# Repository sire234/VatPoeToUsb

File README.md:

# PoE → USB-Host-HID-Bridge (poe_usb_hid_bridge) – Rev 4g

Ein Gerät, das über **ein Ethernet-Kabel mit PoE (IEEE 802.3af)** gespeist wird und an einem **USB-A-Host-Port** ein HID-Gerät (Tastatur, Barcode-Scanner, Maus) betreibt. Die HID-Daten stellt die Firmware über Ethernet bereit.

| | |
|---|---|
| Stand | **Rev 4g** (2026-10-26: MagJack-LEDs wieder beschaltet, R5/R6; Rev 4f: D11 normale grüne LED statt WS2812B, C64 entfällt; Schaltplan mit Leitungen gezeichnet, Pin-1-Punkte im Bestückungsdruck) auf Basis **Rev 4e** inkl. Review-Korrekturen K1/H1, 2026-10-23 · **2. Review (2026-10-23):** Funktion HID → USB → MCU → Ethernet und PoE → 5 V bestätigt, keine KRITISCH/HOCH-Befunde in der Schaltung, K1/H1 verifiziert; Bohrdaten-Nullpunkt, U4-Wärme-Vias und USB-GND-Stitching behoben |
| Board | 20 × 80 mm, 6 Lagen, 1,6 mm (JLC06161H-3313), beidseitig bestückt, für ein **Kunststoffrohr** Innen-Ø 25 mm (**max. 40 °C Umgebung** empfohlen) |
| PoE | Silvertel **Ag9905-LPB** (802.3af Class 0, isoliert 5 V / 1,4 A), Brücken MB6S, TVS SMAJ58A · speisende PSE muss **IEEE 802.3af/at ≥ 48 V** sein (kein passives 24-V-PoE) |
| MCU + Ethernet | WIZnet **W55RP20** (RP2040 + W5500 + 2 MB Flash); 12 MHz Abracon ABM8-272-T3 + 2 × 15 pF (RPi-Referenz); RX über Koppel-C C65/C66 6,8 nF (WIZnet „connected CT") |
| USB | USB-A-Host, TPS2553-Lastschalter (532–659 mA), USBLC6-ESD |
| Status | MagJack-LEDs an J1 (grün = Link ← U5 LINKLED, gelb = Activity ← U5 ACTLED, aktiv low, R5/R6 330 Ω an +3V3) und eine **grüne 0603-LED** D11 (MEIHUA MHT193CGCT, 569 nm) an GPIO28 über R38 330 Ω, High = an (≈ 3,5 mA) |
| Debug | nur **SWD** über Randpads J3 (1 SWCLK, 2 GND, 3 SWDIO, 4 +3V3) für eine 2,54-mm-Stiftleiste |
| Prüfstatus | ERC 0 Fehler / 0 Warnungen · DRC (2026-10-23 13:47) 0 Errors / 0 Unconnected / 0 Parity, 23 Warnungen (nur Silkscreen/Bibliothek) |
| Bauteile | 85 Referenzen / 46 Netze → 75 Positionen bei JLC + U1 beigestellt (9 DNP inkl. J3/U1, TP9 nur Pad) · ≈ 25 USD/Board bei 10 Stk |

## Ordnerstruktur (gültige Dateien)

```text
PoeToUSB/
├── README.md                      dieser Überblick
├── SPEC.md                        Anforderungen (Stand Rev 4e)
├── pipeline_state.json            Pipeline-Status
├── architecture/
│   ├── block_diagram.md           Blöcke B1–B7, Isolationsgrenze
│   ├── net_plan.md                alle Netze, Pin-für-Pin je Block, Netzklassen
│   ├── ic_selection.md            Bauteilwahl und Begründungen
│   ├── skeleton_bom.md            funktionale Stückliste je Block, Auslegung R25
│   ├── power_budget.md            Strom-/Leistungs-/Wärmebudget
│   ├── mechanical_concept.md      Rohr, Höhenhülle, Platzierung, Stackup
│   └── design_risks.md            offene Risiken, Review-Befunde, Entscheidungen OD-1…13
├── sourcing/sourced_bom.md        Einkaufs-BOM (85 Refs, LCSC/MPN/Kosten)
├── datasheets/                    Datenblätter + *_SUMMARY.md, Index README.md
├── circuits/poe_usb_hid_bridge/   SKiDL-Quellcode (Quelle der Wahrheit)
│   ├── __main__.py                Zusammenbau, ERC, Netzlisten-Export
│   ├── ethernet_magjack.py        B1
│   ├── poe_pd_module.py           B2
│   ├── ldo_3v3.py                 B4
│   ├── mcu_w55rp20.py             B5
│   ├── usb_host_port.py           B6
│   └── status_led.py              B7
├── libs/poe_usb_hid_bridge.kicad_sym          Projekt-Symbole
├── footprints/poe_usb_hid_bridge.pretty/      Projekt-Footprints
├── kicad/poe_usb_hid_bridge_rev4g/            KiCad-10-Projekt (Schaltplan mit Leitungen + Board); ältere Revisionen nur noch in der Git-Historie
├── mechanical/
│   ├── gehaeuse_eckig_rev1/                   eckiges Gehäuse (Wanne + Deckel), make_script.py = Quelle beider Varianten
│   └── gehaeuse_eckig_rev1_swd/               dito mit seitlicher Aussparung für die SWD-Stiftleiste J3 (--swd)
├── firmware/                                  Pico-SDK-Firmware (TinyUSB-Host, W5500, mDNS, Ventile), blinky/, hwtest/
├── tools/valve-scan/                          .NET-Tool: Bridges per mDNS finden, Ventile lesen, Dauertest
└── outputs/
    ├── poe_usb_hid_bridge_rev4g.net           Netzliste
    ├── poe_usb_hid_bridge_rev4g_bom.xml       BOM (SKiDL-XML)
    ├── poe_usb_hid_bridge_rev4g_erc.txt       ERC-Protokoll (SKiDL)
    ├── poe_usb_hid_bridge_rev4g_schematic.pdf Schaltplan-PDF (mit Leitungen)
    ├── layout_rev4g/                          3D-Renders (oben, unten, iso, Detail Pin-1-Punkte, R5/R6)
    └── fab_rev4g_release/                     Fertigungsdaten (Gerber, Drill, BOM, CPL) – gültig
```

Ältere Revisionen (Netzlisten, Layouts, Fab-Daten Rev 3–4d, Snapshots) liegen noch im Projekt, gelten aber nicht mehr.

## Projekt öffnen

1. **KiCad 10** starten → `kicad/poe_usb_hid_bridge_rev4g/poe_usb_hid_bridge_rev4g.kicad_pro` öffnen. Die Projekt-Bibliotheken sind über die lokalen `sym-lib-table`/`fp-lib-table` eingebunden.
2. Der Schaltplan ist hierarchisch (ein Sheet je Block: `ethernet_magjack`, `poe_pd_module`, `ldo_3v3`, `mcu_w55rp20`, `usb_host_port`, `status_led`).
3. Netzliste neu erzeugen (optional): in `circuits/` mit installiertem SKiDL `python -m poe_usb_hid_bridge` ausführen → schreibt `outputs/poe_usb_hid_bridge_rev4g.net` und `_bom.xml` (KiCad-10-Bibliothekspfade sind in `__main__.py` gesetzt).

## Fertigungsdaten

Ort: **`outputs/fab_rev4g_release/`** (Gerber, Bohrdaten, JLC-BOM und -CPL, ZIP `poe_usb_hid_bridge_rev4g_gerber_drill.zip`; Stand 2026-10-26; DRC 0 Errors / 0 Unconnected / 0 Parity, 18 Warnungen Silkscreen/J1). **Nicht verwenden:** `fab_rev4f_final/` und `fab_rev4g_final/` – dort liegen die Gerber auf absoluten Koordinaten, die Bohrdaten auf dem Board-Ursprung (100 mm Versatz, Review 2026-10-26). U1 ist im JLC-Export DNP (Beistellteil), J3 (SWD-Randpads), TP9 und alle DNP-Optionen erscheinen nicht in der CPL.

**Behobener Exportfehler (2026-10-23):** Die Bohrdaten hatten einen anderen Nullpunkt als die Gerbers (Versatz 100 mm, Board-Ursprung bei 100/100). Bohrdaten wurden mit `--drill-origin plot` neu exportiert, das ZIP neu gepackt. Bei jedem Neu-Export so vorgehen (KiCad 10, im Ordner `kicad/poe_usb_hid_bridge_rev4e/`):

```text
kicad-cli pcb export gerbers --use-drill-file-origin --layers "F.Cu,In1.Cu,In2.Cu,In3.Cu,In4.Cu,B.Cu,F.Paste,B.Paste,F.Silkscreen,B.Silkscreen,F.Mask,B.Mask,Edge.Cuts" -o ../../outputs/fab_rev4g_release/gerber/ poe_usb_hid_bridge_rev4g.kicad_pcb
kicad-cli pcb export drill --format excellon --drill-origin plot --excellon-separate-th --generate-map --map-format gerberx2 -o ../../outputs/fab_rev4g_release/gerber/ poe_usb_hid_bridge_rev4g.kicad_pcb
```

**Wichtig:** Gerber immer mit `--use-drill-file-origin` exportieren, Bohrdaten mit `--drill-origin plot` – beide liegen dann auf dem Board-Ursprung (Ecke RJ45-Seite, X0 … 80).

- Gerber und Bohrdaten müssen denselben Nullpunkt haben (`plot`); im JLC-Gerber-Viewer prüfen, dass die Bohrungen auf den Pads liegen.
- **Nicht `--board-plot-params` verwenden:** Im Board ist der Plotparameter `drillshape=1` gesetzt → Bohrmarken in den Kupferlagen. Entweder ohne Board-Plotparameter exportieren oder `drillshape` vorher auf 0 setzen.
- **Bei J1 nicht „Footprints aus Bibliothek aktualisieren"**: Der J1-Footprint ist lokal angepasst (verkleinerte Pads/ISO-Keepout, R-ISO-3); die DRC-Warnung `lib_footprint_mismatch` ist deshalb gewollt.
- DRC (13:47): 0 Errors / 0 Unconnected / 0 Parity, 23 Warnungen (Silkscreen, J1-Bibliotheksabgleich).

## Bestell-Checkliste (JLCPCB)

- [ ] **6 Lagen, 1,6 mm, Stackup JLC06161H-3313** wählen; Lagenbelegung In1 GND, In2 VBUS, In3 +5V, In4 +3V3.
- [ ] **Impedanzkontrolle** bestellen: ETH 100 Ω diff. (0,13 / 0,2 mm), USB 90 Ω diff. (0,15 / 0,18 mm) – mit dem JLC-Impedanzrechner für JLC06161H-3313 gegenprüfen.
- [ ] **Vias:** Standard 0,45/0,3 mm; in der Rule-Area `U5_FANOUT` **3 Vias 0,4/0,2 mm mit 0,1 mm Abstand** → entsprechende Fertigungsoption (Aufpreis; optional vorher durch 0,45/0,3 ersetzen, dann entfällt er).
- [ ] **Via-in-Pad gefüllt und gedeckelt (POFV)** – im Board nicht als Attribut gesetzt → bei der Bestellung wählen und diese **POFV-Liste** beilegen (Koordinaten x/y in mm, Board-Ursprung = Ecke RJ45-Seite):
  - *Via-Mitte im Pad:* U1 Pad 1 × 2 (41,6/4,2; 42,4/4,2), C52.1 (62,32/13,56), U4-EP × 3 (49,15/14,04; 49,15/14,60; 49,15/15,16).
  - *Via-Rand berührt Pad:* U5.54 (60,79/12,25), C55.1 (59,34/4,68), R22.1 (57,05/4,2), C50.2 (49,6/10,3).
- [ ] **U1 Ag9905-LPB beistellen** (DigiKey 5061-AG9905-LPB-ND) → JLC-Consignment-SMT, sonst Handreflow; **nur Oberseite**. Für Consignment **U1 in BOM und CPL aufnehmen** (im aktuellen Export DNP).
- [ ] **Paste auf DNP-Pads:** Die Pastenschablone druckt auch auf die Pads von U1, C1, C14, R8, R9, C30 → bei JLC akzeptieren bzw. Hinweis geben (U1-Consignment braucht die Paste).
- [ ] **CPL-Rotationen** sind KiCad-Winkel → im JLC-Placement-Viewer jede Lage prüfen, besonders U5, U4, U6, U7, C11, C18, D1–D3, D12, D11, Y1/Y2. Bei **Y1/Y2 nach Datenblatt-Pin-1 ausrichten, nicht nach der Fase** – eine 90°-Fehllage legt die Quarzpins auf GND.
- [ ] **Lagerbestand (live 2026-10-23):** **W55RP20 C43229502 nur 89 Stk → bei JLC reservieren!** · ABM8-272-T3 C20625731 3 388 · HR871150C C19724786 328 · USB-A C18077687 488. C65/C66 (C93654) und C25/C26 15 pF (C1548) in der JLC-BOM kontrollieren.
- [ ] **D11 grüne LED (C2962098):** Polarität (Kathode = Pad 1, in der Draufsicht unten) im JLC-Placement-Viewer prüfen; kein Backen mehr nötig (WS2812B entfallen).
- [ ] **Footprint-1:1-Prüfungen** mit Ausdruck: U1 (Ag9905-LPB, Pin-1-Lage!), J1 (HR871150C), J2 (BX-TYPE-A-MWT4P); zusätzlich U5-Land-Pattern.
- [ ] J1 ist THT → JLC-THT-Lötservice; **20 Extended-Typen** (≈ 60 USD/Bestellung).
- [ ] **Optional (Review-Empfehlung, Hipot):** R7 statt 0603 als 1206-HV-Widerstand – im aktuellen Board nicht umgesetzt (design_risks R-ISO-8).
- [ ] **Speisung klären:** Router/Switch/Injektor muss **IEEE 802.3af/at mit ≥ 48 V** liefern; passives 24-V-PoE funktioniert nicht.
- [ ] **Gehäuse:** Kunststoffrohr Innen-Ø 25 mm, Endkappen mit Lüftungsschlitzen; Einsatz bei **max. 40 °C Umgebung** einplanen.
- [ ] Vor dem Bestellen Stock/Preise in `sourcing/sourced_bom.md` neu prüfen.

## Inbetriebnahme

1. **Erstes Einschalten:** normgerechter **802.3af/at-PoE-Injektor bzw. -Switch (≥ 48 V)**, idealerweise mit Strombegrenzung – kein passives 24-V-PoE; +5V an TP9 und +3V3 an J3 Pin 4 messen (Erwartung: 4,75–5,25 V bzw. 3,30 V; Leerlauf ≈ 180 mA an +5V_RAW mit Link).
2. **Programmierung nur über SWD:** 1×4-Stiftleiste (2,54 mm) liegend auf die Randpads J3 löten, Pins ragen über die Board-Kante: Pin 1 SWCLK, 2 GND, 3 SWDIO, 4 +3V3. Pins 1–3 entsprechen der SWD-Reihenfolge des Raspberry Pi Pico bzw. des 3-Pin-Kabels der Raspberry Pi Debug Probe (OpenOCD `rp2040.cfg`); +3V3 nur als Referenz, das Board über PoE versorgen. Es gibt keinen BOOTSEL-Taster, kein UART und keinen Reset-Pin – der USB-A-Port ist Host und taugt nicht für den USB-Bootloader.
3. **Firmware:** Pico-SDK + **TinyUSB-Host** (`tuh_hid_*`) + **WIZnet ioLibrary** (W5500 über das interne PIO-SPI des W55RP20; GPIO20–25 intern).
   - GPIO26 = `USB_EN` (aktiv-high, Default AUS), GPIO28 = `LED_DIN` (normaler GPIO-Ausgang, High = grüne LED an; PWM möglich), GPIO29/ADC3 = `VBUS_SENSE` (Faktor 0,405).
   - `PICO_BOARD`, Flash-Grösse 2 MB und boot2 wie beim **WIZnet W55RP20-EVB** einstellen.
   - W5500-Anbindung (verifiziert, WIZnet-PICO-C): CS 20, SCK 21, MISO 22, MOSI 23, INT 24, RST 25 über PIO-SPI (`USE_PIO`). Die Status-LED braucht seit Rev 4f keinen PIO mehr.
   - Überlast über `VBUS_SENSE` erkennen: **Schwelle ≈ 4,0–4,2 V** (nicht 4,5 V – im Normalbetrieb sind Worst Case ≈ 4,6 V möglich), Messwert mitteln und **> 50 ms entprellen**, dann `USB_EN` abschalten (Retry mit Backoff).
   - Nach `USB_EN = 0` entlädt sich VBUS nur über den Teiler (τ ≈ 27 s): vor einem Neustart des Ports warten bzw. per `VBUS_SENSE` prüfen, dass VBUS abgefallen ist.
   - MagJack-LEDs (Rev 4g) werden direkt vom W5500 angesteuert (Link grün, Activity gelb) – keine Firmware nötig. Link-Status zusätzlich über **PHYCFGR** lesbar.
   - Status-LED: ≈ 3,5 mA bei Dauer-An, kein Einfluss auf das +3V3-Budget.
   - Quarz Y1 entspricht der Raspberry-Pi-Referenz (ABM8-272-T3, 2 × 15 pF, 1 kΩ); `PICO_XOSC_STARTUP_DELAY_MULTIPLIER` kann auf dem SDK-Default bleiben (64 als Reserve schadet nicht).
4. Danach PoE vom Ziel-Router/-Switch (802.3af/at, ≥ 48 V): Detection, Link 10/100, USB-Gerät anstecken.
5. **Thermik prüfen:** im geschlossenen Kunststoffrohr bei Volllast (USB 0,5 A) und USB-Kurzschluss die Temperaturen an U1, U5, U4 und J1 messen; Betrieb nur bis **40 °C Umgebung** (W55RP20 Tc ≤ 85 °C, J1 ≤ 70 °C).
6. **R9 (VBUS-Abgleich) nur bei Bedarf:** +5V_RAW höchstens 5,25 V – R9 = 0 Ω (5,65 V) ist unzulässig.

## Offene Prüfpunkte am Muster

| Punkt | Was prüfen | Option |
|---|---|---|
| **Thermik** | Temperatur an U1, U5, U4, J1 im geschlossenen Rohr bei Volllast und USB-Kurzschluss (erwartet ≈ 68–80 °C bei 40 °C Umgebung) | Kunststoffrohr: Umgebung ≤ 40 °C, Lüftungsschlitze in den Endkappen; Isolation zum Rohr unkritisch. U4 hat jetzt 3 Thermal-Vias im EP + 2 GND-Vias |
| **VBUS / R9** | VBUS am Port unter 0,5 A (Worst Case ≈ 4,6 V) | R9 ADJ → GND bestücken, Ziel +5V_RAW ≈ 5,10 V, **max. 5,25 V** (R9 = 0 Ω → 5,65 V unzulässig) |
| **PoE-Detection / C1** | Detection mit 2–3 verschiedenen PSEs | C1 bleibt DNP; nur bei Bedarf bestücken |
| **Hipot 1500 VAC** | Isolation primär ↔ sekundär inkl. J1-Pfad (R-ISO-3, R-ISO-7, ETH_RXN 1,8 mm zu J1.7 R-ISO-9); Modul ist für 1500-V-DC-Impuls spezifiziert | C24 DNP als Option; R7 0603 ist im Hipot überlastet → 1206-HV empfohlen (R-ISO-8) |
| **Mindestlast / R8** | Geräusch im Leerlauf (< 200 mA) | R8 100 Ω (1206) bestücken |
| **RUN-Pull-up** | Störfestigkeit ohne externen Reset-Pull-up/C | 10 k (+ 100 nF) von RUN (U5.29) an +3V3 nachrüsten |
| **Ethernet** | Link 10/100, Paketverlust bei 100 m (RX jetzt mit C65/C66); W5500-Stabilität (C61 nicht direkt an TOCAP, Abblock Pin 42/43 > 5 mm) | siehe design_risks R-ETH-1, R-LAY-7, R-PI-12 |
| **Mechanik** | D3 (SMA, Bottom) hat nur ≈ 0,25 mm Reserve zur Rohrwand; J2 laut Datenblatt 15,2 mm breit (Laschen) / 7,0 mm hoch | Einbau ins Rohr vorsichtig prüfen |
| Weitere | Quarz-Anlauf kurz kontrollieren, USB-Signalqualität, LED-Helligkeit an 3,3 V, D11-Polarität | siehe `architecture/design_risks.md` §4 (offene Review-Empfehlungen) |

## Revisionsverlauf (Kurz)

Rev 1–3 diskreter Flyback (TPS23753A + POE70P) · Rev 3 30-mm-Board verworfen · Rev 4 Ag9905LP-Modul · Rev 4b WS2812B + Tag-Connect · Rev 4c Brücken-Variante verworfen · Rev 4d Minimal-Debug (nur SWD), LED an +3V3 · **Rev 4e Ag9905-LPB (SMT)** · Rev 4e Review: K1 RX-Koppel-C C65/C66, H1 Quarz nach RPi-Referenz, Kunststoffrohr ≤ 40 °C · **Rev 4f** D11 normale grüne LED (C64 entfällt), ganzer Schaltplan mit Leitungen, Pin-1-Punkte, 3D-Modelle U1/U5/J1/J2 · **Rev 4g** MagJack-LEDs wieder beschaltet (R5/R6, Leitungen auf In3).

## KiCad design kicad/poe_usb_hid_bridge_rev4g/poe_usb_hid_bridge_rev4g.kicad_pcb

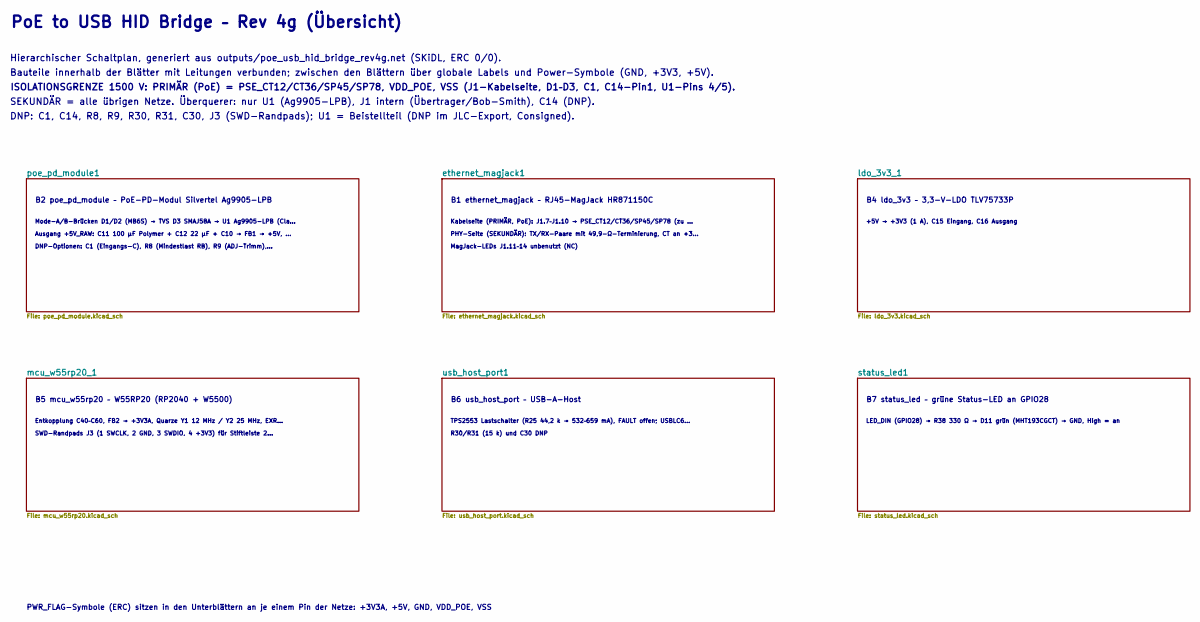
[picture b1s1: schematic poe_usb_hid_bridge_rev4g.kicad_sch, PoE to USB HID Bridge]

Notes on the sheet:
PoE to USB HID Bridge – Rev 4g (Übersicht)
Hierarchischer Schaltplan, generiert aus outputs/poe_usb_hid_bridge_rev4g.net (SKiDL, ERC 0/0).
Bauteile innerhalb der Blätter mit Leitungen verbunden; zwischen den Blättern über globale Labels und Power-Symbole (GND, +3V3, +5V).
ISOLATIONSGRENZE 1500 V: PRIMÄR (PoE) = PSE_CT12/CT36/SP45/SP78, VDD_POE, VSS (J1-Kabelseite, D1–D3, C1, C14-Pin1, U1-Pins 4/5).
SEKUNDÄR = alle übrigen Netze. Überquerer: nur U1 (Ag9905-LPB), J1 intern (Übertrager/Bob-Smith), C14 (DNP).
DNP: C1, C14, R8, R9, R30, R31, C30, J3 (SWD-Randpads); U1 = Beistellteil (DNP im JLC-Export, Consigned).
B2 poe_pd_module – PoE-PD-Modul Silvertel Ag9905-LPB
Mode-A/B-Brücken D1/D2 (MB6S) → TVS D3 SMAJ58A → U1 Ag9905-LPB (Cla…
Ausgang +5V_RAW: C11 100 µF Polymer + C12 22 µF + C10 → FB1 → +5V, …
DNP-Optionen: C1 (Eingangs-C), R8 (Mindestlast RB), R9 (ADJ-Trimm),…
B1 ethernet_magjack – RJ45-MagJack HR871150C
Kabelseite (PRIMÄR, PoE): J1.7–J1.10 → PSE_CT12/CT36/SP45/SP78 (zu …
PHY-Seite (SEKUNDÄR): TX/RX-Paare mit 49,9-Ω-Terminierung, CT an +3…
MagJack-LEDs J1.11–14 unbenutzt (NC)
B4 ldo_3v3 – 3,3-V-LDO TLV75733P
+5V → +3V3 (1 A), C15 Eingang, C16 Ausgang
B5 mcu_w55rp20 – W55RP20 (RP2040 + W5500)
Entkopplung C40–C60, FB2 → +3V3A, Quarze Y1 12 MHz / Y2 25 MHz, EXR…
SWD-Randpads J3 (1 SWCLK, 2 GND, 3 SWDIO, 4 +3V3) für Stiftleiste 2…
B6 usb_host_port – USB-A-Host
TPS2553 Lastschalter (R25 44,2 k → 532–659 mA), FAULT offen; USBLC6…
R30/R31 (15 k) und C30 DNP
B7 status_led – grüne Status-LED an GPIO28
LED_DIN (GPIO28) → R38 330 Ω → D11 grün (MHT193CGCT) → GND, High = an
PWR_FLAG-Symbole (ERC) sitzen in den Unterblättern an je einem Pin der Netze: +3V3A, +5V, GND, VDD_POE, VSS

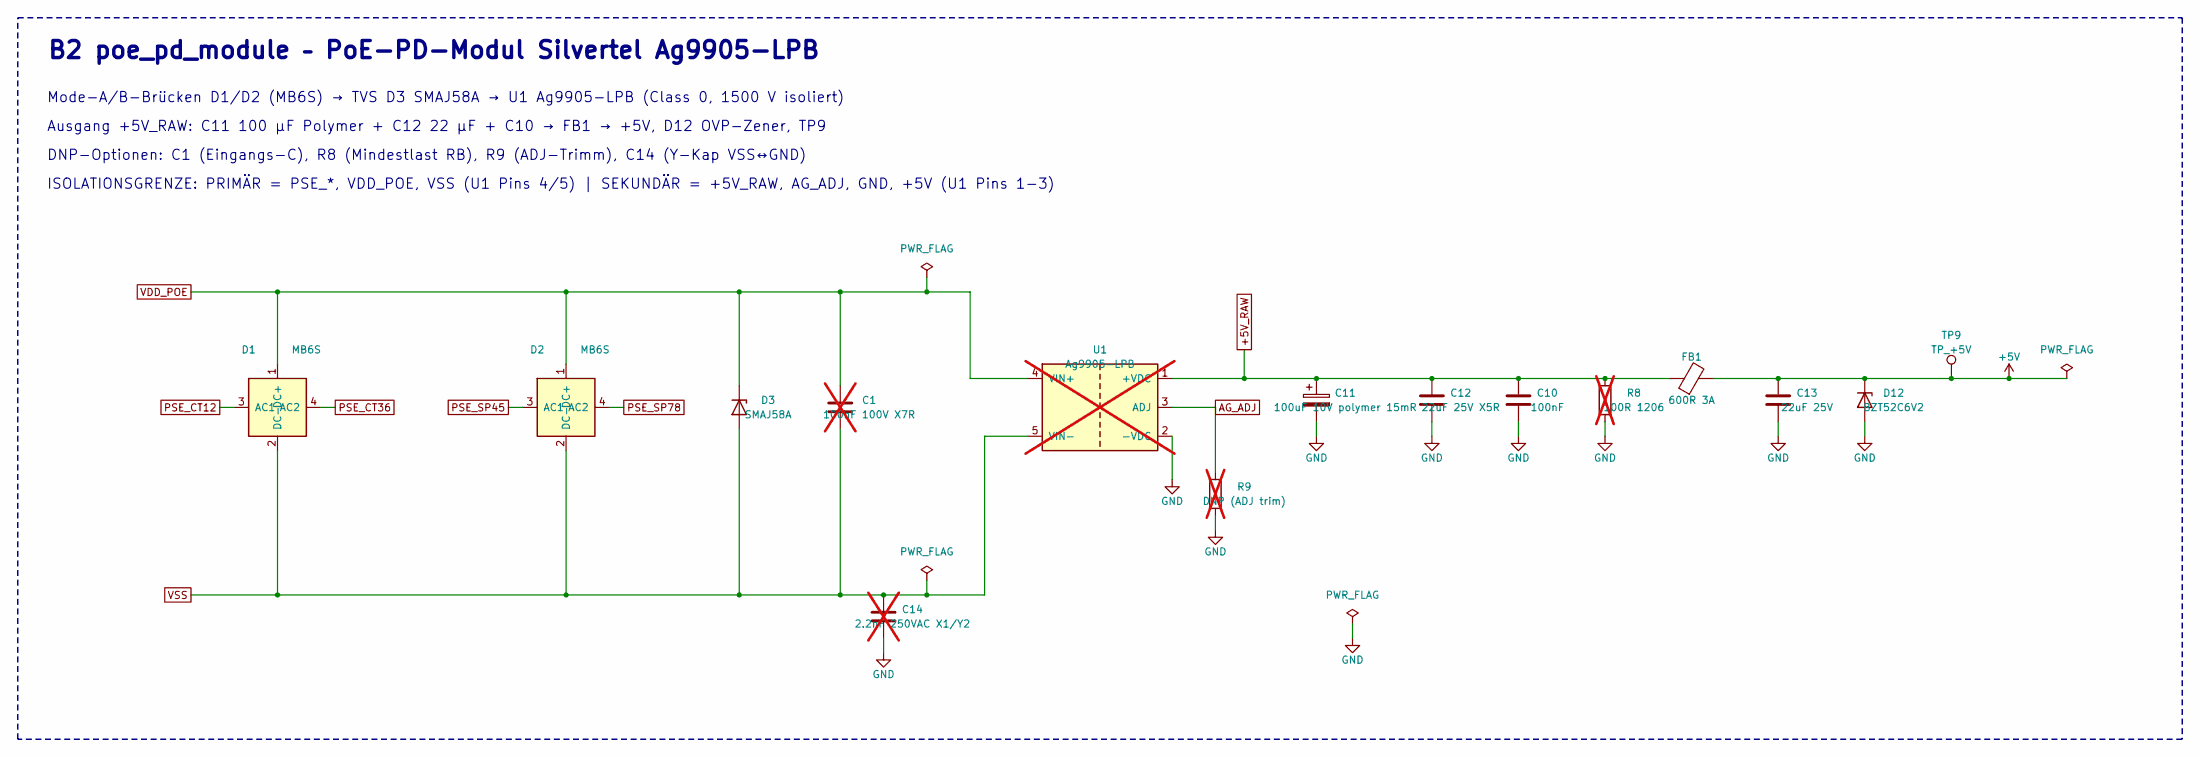
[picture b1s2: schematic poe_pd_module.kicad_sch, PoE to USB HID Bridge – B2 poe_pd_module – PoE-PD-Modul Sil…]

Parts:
C1: 100nF 100V X7R; C_0805_2012Metric; MPN CL21B104KCFNNNE; LCSC C28233; not fitted
C10: 100nF; C_0402_1005Metric; MPN CL05B104KO5NNNC; LCSC C1525
C11: 100uF 10V polymer 15mR; CP_EIA-7343-31_Kemet-D; MPN SA11AM101A19R15XXX; LCSC C135491
C12: 22uF 25V X5R; C_0805_2012Metric; MPN CL21A226MAQNNNE; LCSC C45783
C13: 22uF 25V; C_0805_2012Metric; MPN CL21A226MAQNNNE; LCSC C45783
C14: 2.2nF 250VAC X1/Y2; C_1812_4532Metric; MPN FK12X222K502EGQ; LCSC C53026446; not fitted
D1, D2: MB6S; TO-269AA; MPN MDD MB6S-50MIL; LCSC C2487
D3: SMAJ58A; D_SMA; MPN MDD SMAJ58A; LCSC C123816
D12: BZT52C6V2; D_SOD-123; MPN BZT52C6V2; LCSC C271260
FB1: 600R 3A; L_1206_3216Metric; MPN HCB3216KF-601T30; LCSC C357023
R8: 100R 1206; R_1206_3216Metric; MPN 1206W4F1000T5E; LCSC C17901; not fitted
R9: DNP (ADJ trim); R_0603_1608Metric; not fitted
TP9: TP_+5V; TestPoint_Pad_D1.0mm
U1: Ag9905-LPB; Silvertel_Ag9900LPB_SMD; MPN Ag9905-LPB; not fitted

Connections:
+5V: C13.1, D12.1 (K), FB1.2, TP9.1; also elsewhere on the board
+5V_RAW: C10.1, C11.1, C12.1, FB1.1, R8.1, U1.1 (+VDC)
AG_ADJ: R9.1, U1.3 (ADJ)
GND: C10.2, C11.2, C12.2, C13.2, C14.2, D12.2 (A), R8.2, R9.2, U1.2 (-VDC); also elsewhere on the board
PSE_CT12: D1.3 (AC1); also elsewhere on the board
PSE_CT36: D1.4 (AC2); also elsewhere on the board
PSE_SP45: D2.3 (AC1); also elsewhere on the board
PSE_SP78: D2.4 (AC2); also elsewhere on the board
VDD_POE: C1.1, D1.1 (DC+), D2.1 (DC+), D3.1 (K), U1.4 (VIN+)
VSS: C1.2, C14.1, D1.2 (DC-), D2.2 (DC-), D3.2 (A), U1.5 (VIN-)

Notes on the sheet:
B2 poe_pd_module – PoE-PD-Modul Silvertel Ag9905-LPB
Mode-A/B-Brücken D1/D2 (MB6S) → TVS D3 SMAJ58A → U1 Ag9905-LPB (Class 0, 1500 V isoliert)
Ausgang +5V_RAW: C11 100 µF Polymer + C12 22 µF + C10 → FB1 → +5V, D12 OVP-Zener, TP9
DNP-Optionen: C1 (Eingangs-C), R8 (Mindestlast RB), R9 (ADJ-Trimm), C14 (Y-Kap VSS↔GND)
ISOLATIONSGRENZE: PRIMÄR = PSE_*, VDD_POE, VSS (U1 Pins 4/5) | SEKUNDÄR = +5V_RAW, AG_ADJ, GND, +5V (U1 Pins 1-3)

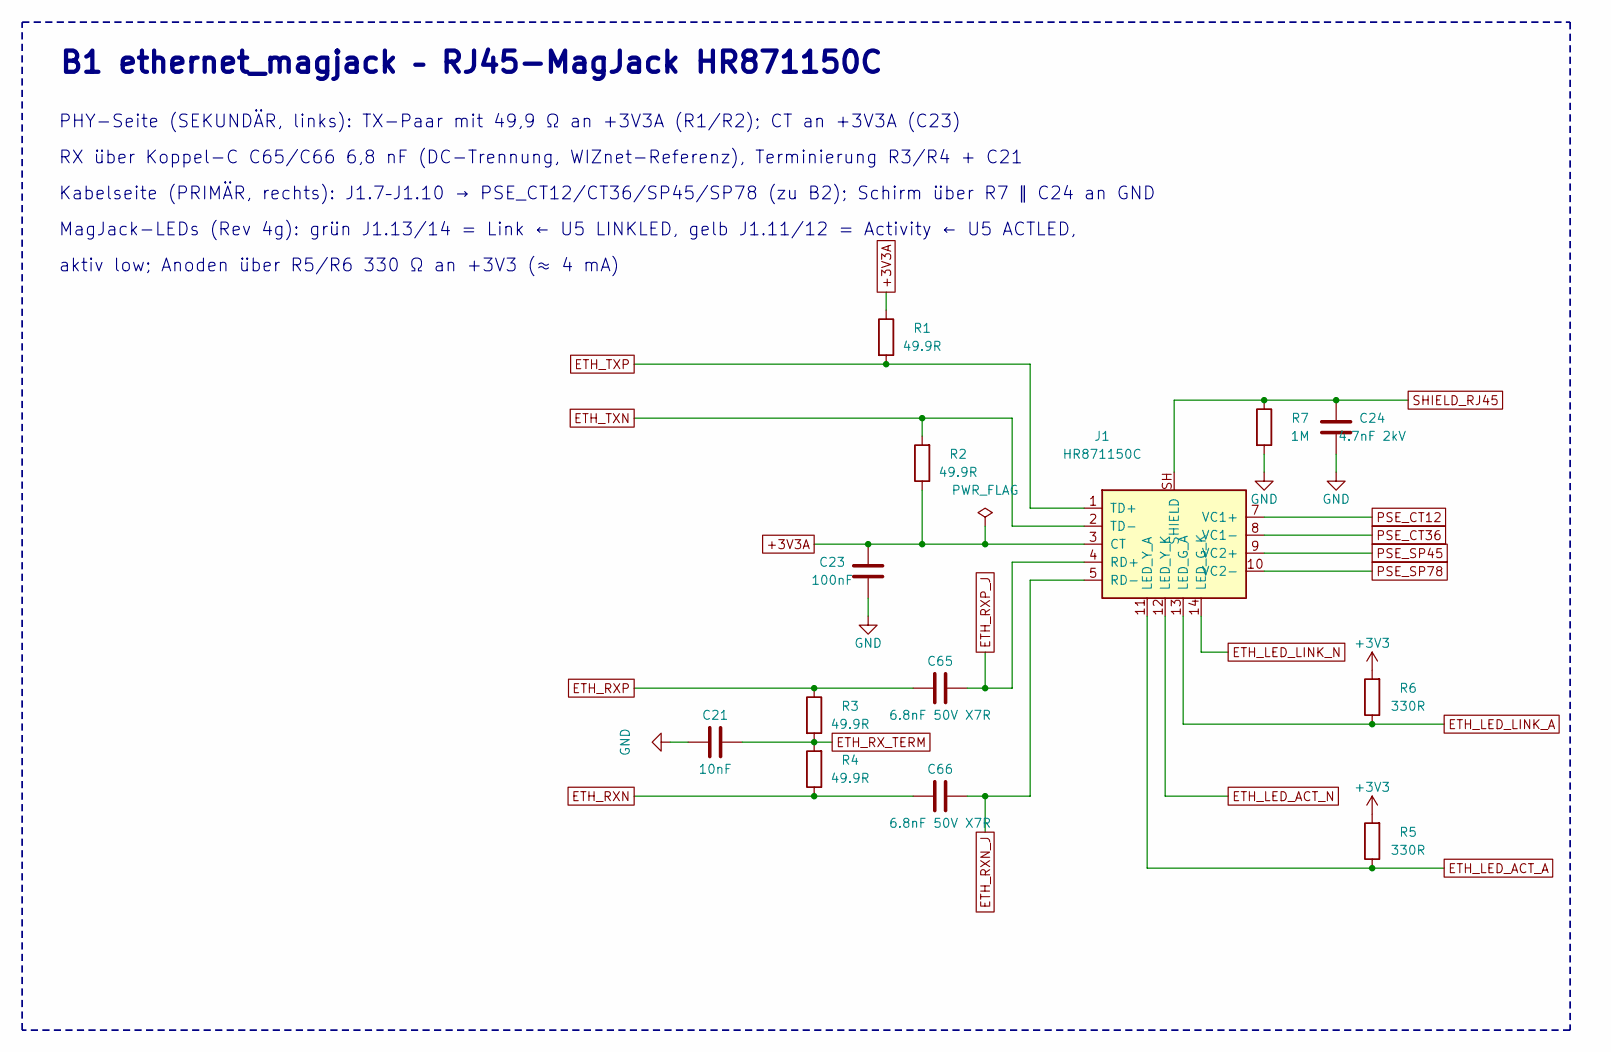
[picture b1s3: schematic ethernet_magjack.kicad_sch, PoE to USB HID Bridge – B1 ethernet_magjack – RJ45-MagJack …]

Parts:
C21: 10nF; C_0402_1005Metric; MPN CL05B103KB5NNNC; LCSC C15195
C23: 100nF; C_0402_1005Metric; MPN CL05B104KO5NNNC; LCSC C1525
C24: 4.7nF 2kV; C_1812_4532Metric; MPN C1812X472K202T; LCSC C106172
C65, C66: 6.8nF 50V X7R; C_0402_1005Metric; MPN YAGEO CC0402KRX7R9BB682; LCSC C93654
J1: HR871150C; HanRun_HR871150C; MPN HanRun HR871150C; LCSC C19724786
R1, R2, R3, R4: 49.9R; R_0402_1005Metric; MPN 0402WGF499JTCE; LCSC C25120
R5, R6: 330R; R_0402_1005Metric; MPN 0402WGF3300TCE; LCSC C25104
R7: 1M; R_0603_1608Metric; MPN 0603WAF1004T5E; LCSC C22935

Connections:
+3V3: R5.2, R6.2; also elsewhere on the board
+3V3A: C23.1, J1.3 (CT), R1.1, R2.1; also elsewhere on the board
ETH_LED_ACT_A: J1.11 (LED_Y_A), R5.1
ETH_LED_ACT_N: J1.12 (LED_Y_K); also elsewhere on the board
ETH_LED_LINK_A: J1.13 (LED_G_A), R6.1
ETH_LED_LINK_N: J1.14 (LED_G_K); also elsewhere on the board
ETH_RXN: C66.2, R4.1; also elsewhere on the board
ETH_RXN_J: C66.1, J1.5 (RD-)
ETH_RXP: C65.2, R3.1; also elsewhere on the board
ETH_RXP_J: C65.1, J1.4 (RD+)
ETH_RX_TERM: C21.1, R3.2, R4.2
ETH_TXN: J1.2 (TD-), R2.2; also elsewhere on the board
ETH_TXP: J1.1 (TD+), R1.2; also elsewhere on the board
GND: C21.2, C23.2, C24.2, R7.2; also elsewhere on the board
PSE_CT12: J1.7 (VC1+); also elsewhere on the board
PSE_CT36: J1.8 (VC1-); also elsewhere on the board
PSE_SP45: J1.9 (VC2+); also elsewhere on the board
PSE_SP78: J1.10 (VC2-); also elsewhere on the board
SHIELD_RJ45: C24.1, J1.SH (SHIELD), R7.1

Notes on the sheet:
B1 ethernet_magjack – RJ45-MagJack HR871150C
PHY-Seite (SEKUNDÄR, links): TX-Paar mit 49,9 Ω an +3V3A (R1/R2); CT an +3V3A (C23)
RX über Koppel-C C65/C66 6,8 nF (DC-Trennung, WIZnet-Referenz), Terminierung R3/R4 + C21
Kabelseite (PRIMÄR, rechts): J1.7–J1.10 → PSE_CT12/CT36/SP45/SP78 (zu B2); Schirm über R7 ∥ C24 an GND
MagJack-LEDs (Rev 4g): grün J1.13/14 = Link ← U5 LINKLED, gelb J1.11/12 = Activity ← U5 ACTLED,
aktiv low; Anoden über R5/R6 330 Ω an +3V3 (≈ 4 mA)

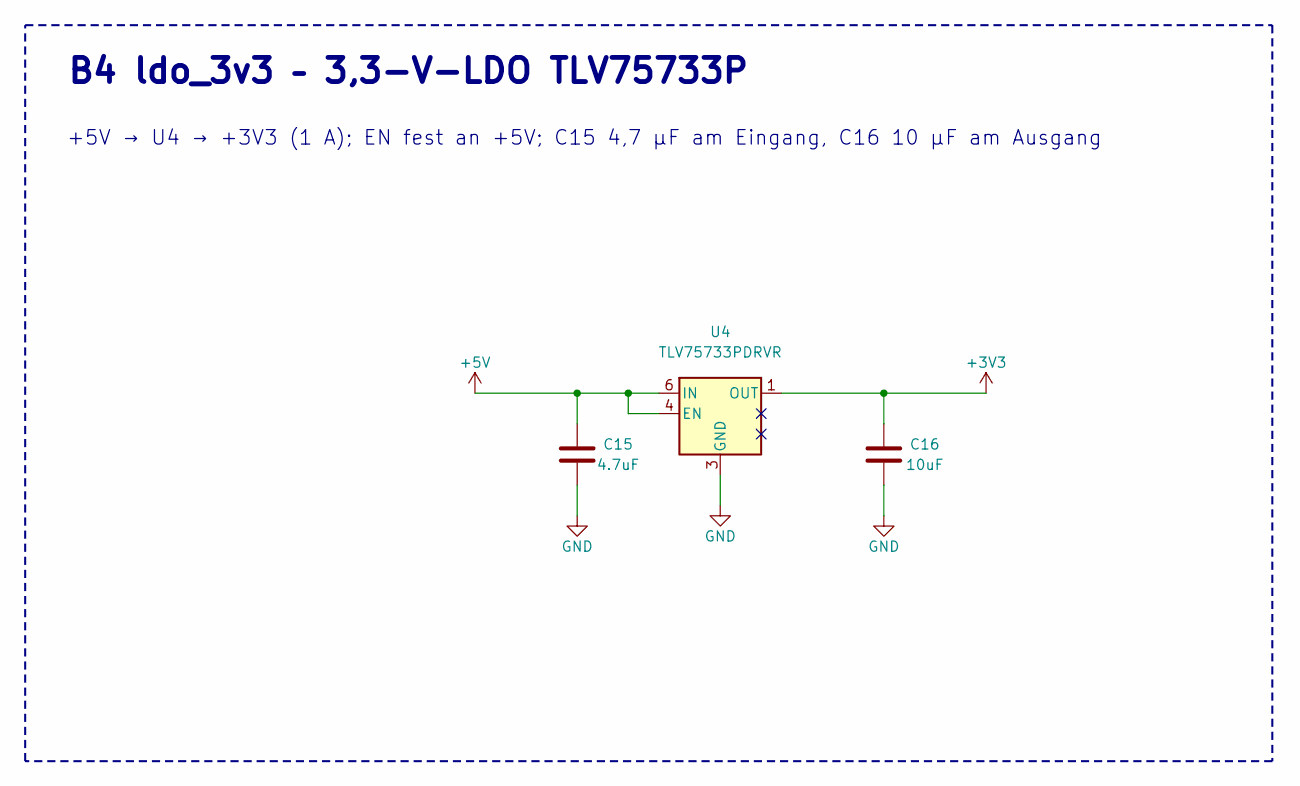
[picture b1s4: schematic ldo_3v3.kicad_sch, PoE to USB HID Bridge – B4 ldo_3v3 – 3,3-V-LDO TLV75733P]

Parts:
C15: 4.7uF; C_0603_1608Metric; MPN CL10A475KO8NNNC; LCSC C19666
C16: 10uF; C_0603_1608Metric; MPN CL10A106KP8NNNC; LCSC C19702
U4: TLV75733PDRVR; WSON-6-1EP_2x2mm_P0.65mm_EP1x1.6mm; MPN TLV75733PDRVR; LCSC C2868428

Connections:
+3V3: C16.1, U4.1 (OUT); also elsewhere on the board
+5V: C15.1, U4.4 (EN), U4.6 (IN); also elsewhere on the board
GND: C15.2, C16.2, U4.3 (GND), U4.7 (GND); also elsewhere on the board

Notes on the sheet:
B4 ldo_3v3 – 3,3-V-LDO TLV75733P
+5V → U4 → +3V3 (1 A); EN fest an +5V; C15 4,7 µF am Eingang, C16 10 µF am Ausgang

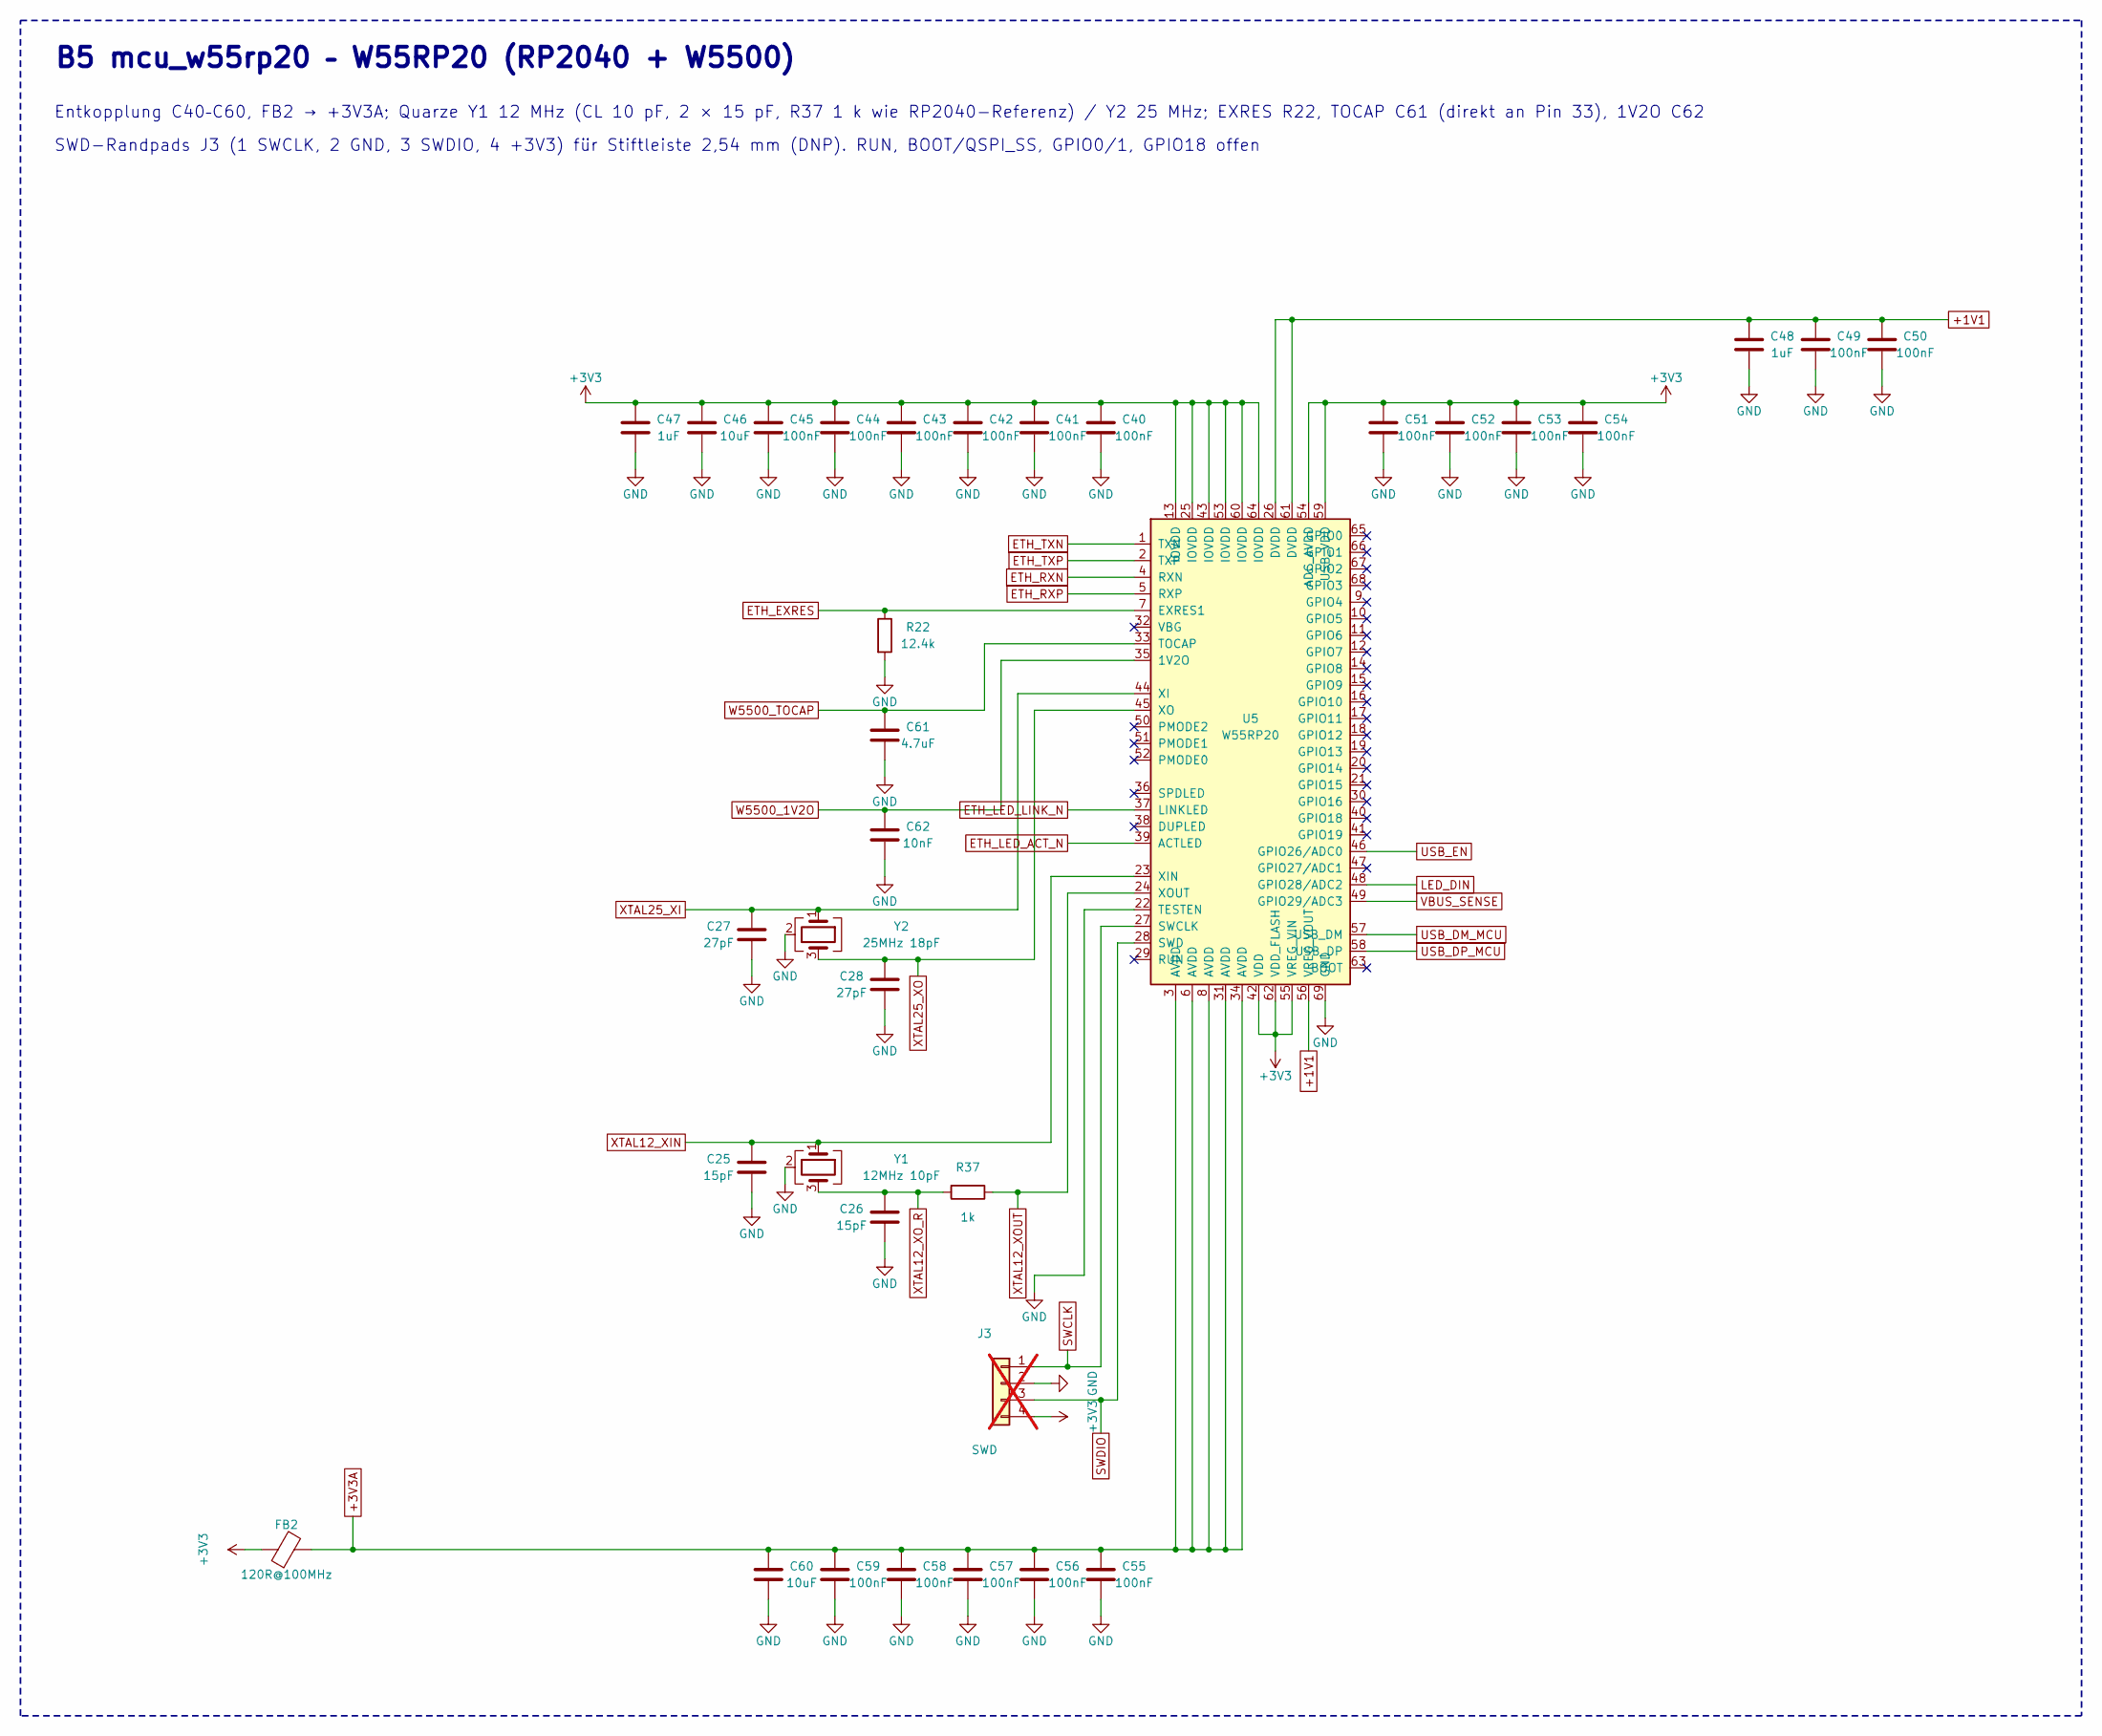
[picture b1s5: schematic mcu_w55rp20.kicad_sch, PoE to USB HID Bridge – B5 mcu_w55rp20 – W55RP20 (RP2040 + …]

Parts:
C25, C26: 15pF; C_0402_1005Metric; MPN 0402CG150J500NT; LCSC C1548
C27, C28: 27pF; C_0402_1005Metric; MPN 0402CG270J500NT; LCSC C1557
C40, C41, C42, C43, C44, C45, C49, C50, C51, C52, C53, C54, C55, C56, C57, C58, C59: 100nF; C_0402_1005Metric; MPN CL05B104KO5NNNC; LCSC C1525
C46, C60: 10uF; C_0603_1608Metric; MPN CL10A106KP8NNNC; LCSC C19702
C47, C48: 1uF; C_0402_1005Metric; MPN CL05A105KA5NQNC; LCSC C52923
C61: 4.7uF; C_0603_1608Metric; MPN CL10A475KO8NNNC; LCSC C19666
C62: 10nF; C_0402_1005Metric; MPN CL05B103KB5NNNC; LCSC C15195
FB2: 120R@100MHz; L_0603_1608Metric; MPN BLM18PG121SN1D; LCSC C14709
J3: SWD; SWD_Edge_1x04_P2.54mm_SMD; not fitted
R22: 12.4k; R_0402_1005Metric; MPN 0402WGF1242TCE; LCSC C11692
R37: 1k; R_0402_1005Metric; MPN 0402WGF1001TCE; LCSC C11702
U5: W55RP20; W55RP20_QFN-68-1EP_8x8mm_P0.4mm_EP6.2x6.2mm; MPN W55RP20; LCSC C43229502
Y1: 12MHz 10pF; Crystal_SMD_3225-4Pin_3.2x2.5mm; MPN Abracon ABM8-272-T3; LCSC C20625731
Y2: 25MHz 18pF; Crystal_SMD_3225-4Pin_3.2x2.5mm; MPN X322525MRB4SI; LCSC C70593

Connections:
+1V1: C48.1, C49.1, C50.1, U5.26 (DVDD), U5.56 (VREG_VOUT), U5.61 (DVDD)
+3V3: C40.1, C41.1, C42.1, C43.1, C44.1, C45.1, C46.1, C47.1, C51.1, C52.1, C53.1, C54.1, FB2.1, J3.4, U5.13 (IOVDD), U5.25 (IOVDD), U5.42 (VDD), U5.43 (IOVDD), U5.53 (IOVDD), U5.54 (ADC_AVDD), U5.55 (VREG_VIN), U5.59 (USB_VDD), U5.60 (IOVDD), U5.62 (VDD_FLASH), U5.64 (IOVDD); also elsewhere on the board
+3V3A: C55.1, C56.1, C57.1, C58.1, C59.1, C60.1, FB2.2, U5.3 (AVDD), U5.6 (AVDD), U5.8 (AVDD), U5.31 (AVDD), U5.34 (AVDD); also elsewhere on the board
ETH_EXRES: R22.1, U5.7 (EXRES1)
ETH_LED_ACT_N: U5.39 (ACTLED); also elsewhere on the board
ETH_LED_LINK_N: U5.37 (LINKLED); also elsewhere on the board
ETH_RXN: U5.4 (RXN); also elsewhere on the board
ETH_RXP: U5.5 (RXP); also elsewhere on the board
ETH_TXN: U5.1 (TXN); also elsewhere on the board
ETH_TXP: U5.2 (TXP); also elsewhere on the board
GND: C25.2, C26.2, C27.2, C28.2, C40.2, C41.2, C42.2, C43.2, C44.2, C45.2, C46.2, C47.2, C48.2, C49.2, C50.2, C51.2, C52.2, C53.2, C54.2, C55.2, C56.2, C57.2, C58.2, C59.2, C60.2, C61.2, C62.2, J3.2, R22.2, U5.22 (TESTEN), U5.69 (GND), Y1.2 (G), Y1.4 (G), Y2.2 (G), Y2.4 (G); also elsewhere on the board
LED_DIN: U5.48 (GPIO28/ADC2); also elsewhere on the board
SWCLK: J3.1, U5.27 (SWCLK)
SWDIO: J3.3, U5.28 (SWD)
USB_DM_MCU: U5.57 (USB_DM); also elsewhere on the board
USB_DP_MCU: U5.58 (USB_DP); also elsewhere on the board
USB_EN: U5.46 (GPIO26/ADC0); also elsewhere on the board
VBUS_SENSE: U5.49 (GPIO29/ADC3); also elsewhere on the board
W5500_1V2O: C62.1, U5.35 (1V2O)
W5500_TOCAP: C61.1, U5.33 (TOCAP)
XTAL12_XIN: C25.1, U5.23 (XIN), Y1.1
XTAL12_XOUT: R37.1, U5.24 (XOUT)
XTAL12_XO_R: C26.1, R37.2, Y1.3
XTAL25_XI: C27.1, U5.44 (XI), Y2.1
XTAL25_XO: C28.1, U5.45 (XO), Y2.3

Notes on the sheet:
B5 mcu_w55rp20 – W55RP20 (RP2040 + W5500)
Entkopplung C40–C60, FB2 → +3V3A; Quarze Y1 12 MHz (CL 10 pF, 2 × 15 pF, R37 1 k wie RP2040-Referenz) / Y2 25 MHz; EXRES R22, TOCAP C61 (direkt an Pin 33), 1V2O C62
SWD-Randpads J3 (1 SWCLK, 2 GND, 3 SWDIO, 4 +3V3) für Stiftleiste 2,54 mm (DNP). RUN, BOOT/QSPI_SS, GPIO0/1, GPIO18 offen

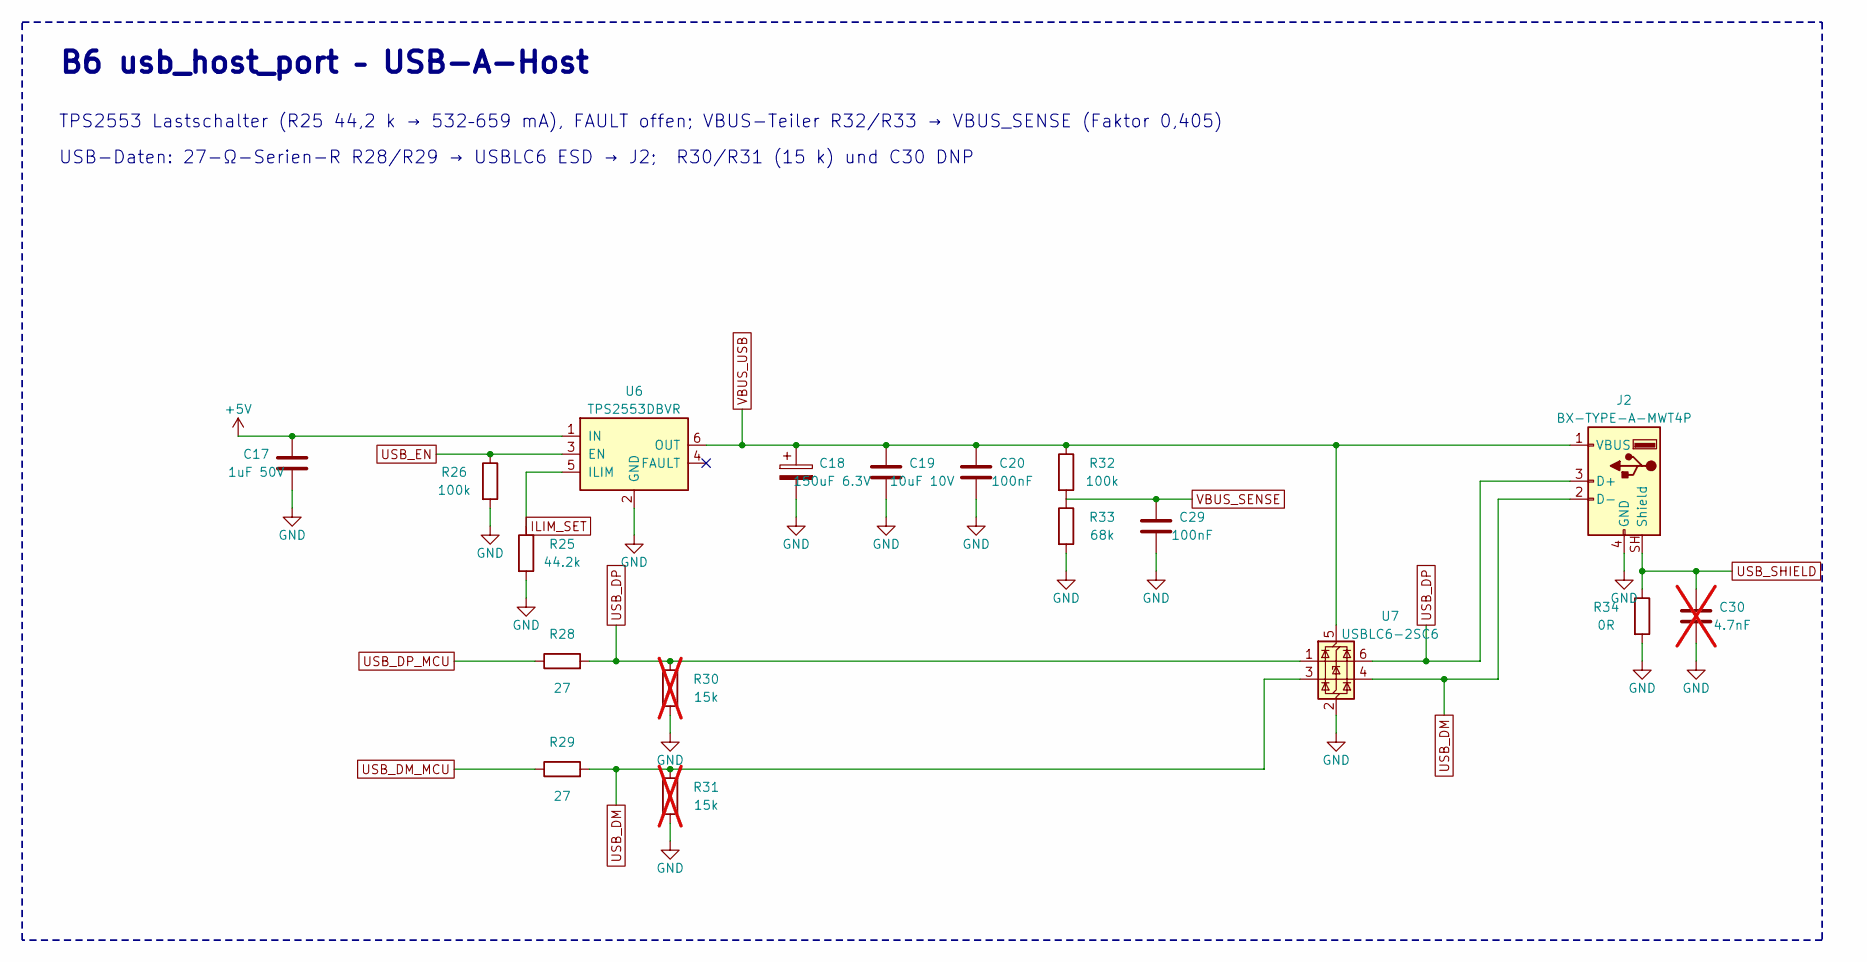
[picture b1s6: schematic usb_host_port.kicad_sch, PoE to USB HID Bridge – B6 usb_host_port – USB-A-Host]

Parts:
C17: 1uF 50V; C_0603_1608Metric; MPN CL10A105KB8NNNC; LCSC C15849
C18: 150uF 6.3V; CP_EIA-3528-21_Kemet-B; MPN T520B157M006ATE035; LCSC C212682
C19: 10uF 10V; C_0603_1608Metric; MPN CL10A106KP8NNNC; LCSC C19702
C20, C29: 100nF; C_0402_1005Metric; MPN CL05B104KO5NNNC; LCSC C1525
C30: 4.7nF; C_0603_1608Metric; MPN CL10B472KB8NNNC; LCSC C1621; not fitted
J2: BX-TYPE-A-MWT4P; MPN BX-TYPE-A-MWT4P; LCSC C18077687
R25: 44.2k; R_0402_1005Metric; MPN 0402WGF4422TCE; LCSC C25895
R26, R32: 100k; R_0402_1005Metric; MPN 0402WGF1003TCE; LCSC C25741
R28, R29: 27; R_0402_1005Metric; MPN 0402WGF270JTCE; LCSC C25100
R30, R31: 15k; R_0402_1005Metric; MPN 0402WGF1502TCE; LCSC C25756; not fitted
R33: 68k; R_0402_1005Metric; MPN 0402WGF6802TCE; LCSC C36871
R34: 0R; R_0603_1608Metric; MPN 0603WAF0000T5E; LCSC C21189
U6: TPS2553DBVR; SOT-23-6; MPN TPS2553DBVR; LCSC C55266
U7: USBLC6-2SC6; SOT-23-6; MPN USBLC6-2SC6; LCSC C7519

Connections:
+5V: C17.1, U6.1 (IN); also elsewhere on the board
GND: C17.2, C18.2, C19.2, C20.2, C29.2, C30.2, J2.4 (GND), R25.2, R26.2, R30.2, R31.2, R33.2, R34.2, U6.2 (GND), U7.2 (GND); also elsewhere on the board
ILIM_SET: R25.1, U6.5 (ILIM)
USB_DM: J2.2 (D-), R29.2, R31.1, U7.3 (I/O2), U7.4 (I/O2)
USB_DM_MCU: R29.1; also elsewhere on the board
USB_DP: J2.3 (D+), R28.2, R30.1, U7.1 (I/O1), U7.6 (I/O1)
USB_DP_MCU: R28.1; also elsewhere on the board
USB_EN: R26.1, U6.3 (EN); also elsewhere on the board
USB_SHIELD: C30.1, J2.SH (Shield), R34.1
VBUS_SENSE: C29.1, R32.2, R33.1; also elsewhere on the board
VBUS_USB: C18.1, C19.1, C20.1, J2.1 (VBUS), R32.1, U6.6 (OUT), U7.5 (VBUS)

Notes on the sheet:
B6 usb_host_port – USB-A-Host
TPS2553 Lastschalter (R25 44,2 k → 532–659 mA), FAULT offen; VBUS-Teiler R32/R33 → VBUS_SENSE (Faktor 0,405)
USB-Daten: 27-Ω-Serien-R R28/R29 → USBLC6 ESD → J2; R30/R31 (15 k) und C30 DNP

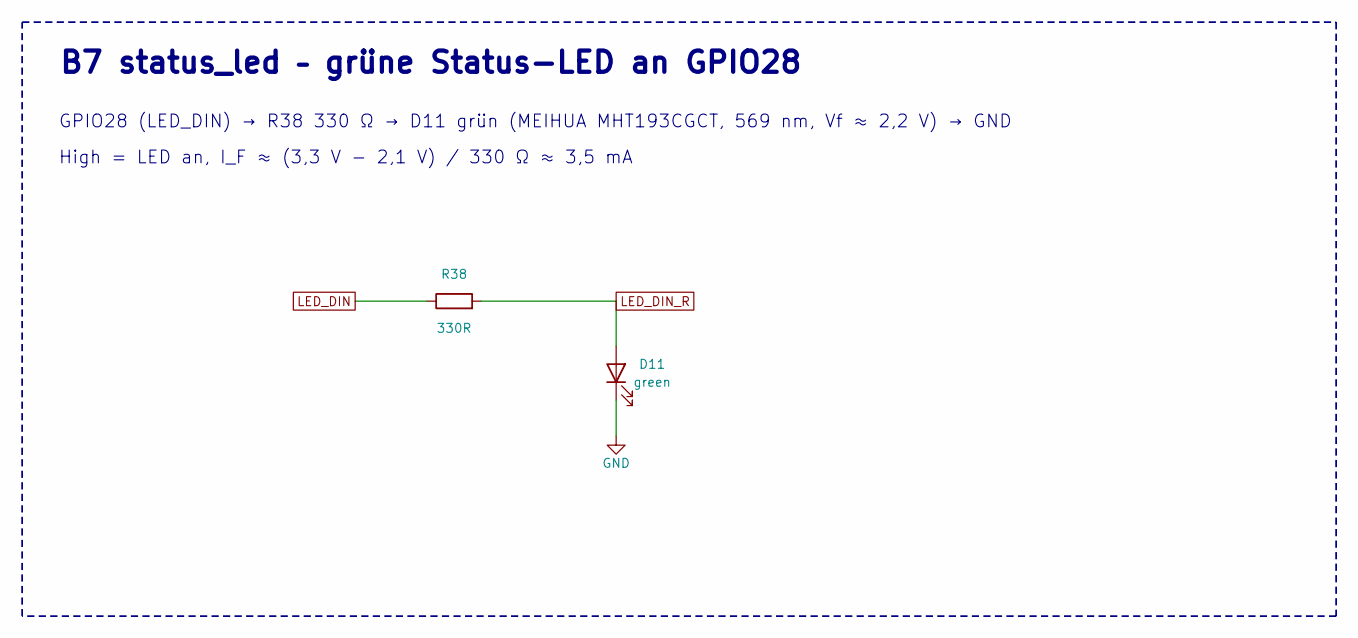
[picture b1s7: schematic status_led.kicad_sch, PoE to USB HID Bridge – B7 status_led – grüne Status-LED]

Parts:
D11: green; LED_0603_1608Metric; MPN MEIHUA MHT193CGCT; LCSC C2962098
R38: 330R; R_0402_1005Metric; MPN 0402WGF3300TCE; LCSC C25104

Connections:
GND: D11.1 (K); also elsewhere on the board
LED_DIN: R38.1; also elsewhere on the board
LED_DIN_R: D11.2 (A), R38.2

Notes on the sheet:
B7 status_led – grüne Status-LED an GPIO28
GPIO28 (LED_DIN) → R38 330 Ω → D11 grün (MEIHUA MHT193CGCT, 569 nm, Vf ≈ 2,2 V) → GND
High = LED an, I_F ≈ (3,3 V − 2,1 V) / 330 Ω ≈ 3,5 mA
